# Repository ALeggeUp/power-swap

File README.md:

# PowerSwap

Project work from The Online Electronics Aprenticeship program at [Contextual Electronics](https://contextualelectronics.com/)

# License

This work is licensed under the Creative Commons Attribution 4.0 International License. To view a copy of this license, visit http://creativecommons.org/licenses/by/4.0/ or send a letter to Creative Commons, PO Box 1866, Mountain View, CA 94042, USA.

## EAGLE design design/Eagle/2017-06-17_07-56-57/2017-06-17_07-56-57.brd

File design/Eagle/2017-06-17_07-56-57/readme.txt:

**********************************************************
*************  Important Instructions Follow  ************
**********************************************************
 
All files exported to: Z:\\29\\16\\291644\\6\Eagle\2017-06-17_07-56-57\2017-06-17_07-56-57.xml

**********************************************************
*****************Schematic Instructions  *******************
**********************************************************

To import your new Schematic file into Eagle:

1. Unzip the downloaded folder files to local directory and Start Eagle.
2. Select "File"->"Open"->"Schematic..." from the menu at the top of
the screen.
3. Browse to your newly exported file and select the ".sch" file extension.
4. You should now see your schamtic available in Eagle.

**********************************************************
*******************  PCB Instructions  *******************
**********************************************************

To import your new BOARD file into Eagle:

1. Unzip the downloaded folder files to local directory and Start Eagle.
2. Select "File"->"Open"->"Board..." from the menu at the top of
the screen.
3. Browse to your newly exported file and select the ".brd" file extension.
4. Planes will need to be repoured to update the polygon fills
	1. Once your board is loaded, type "ratsnest" into the command
	   line and press the Enter key.
	2. The polygons should all be filled now.
5. You should now have an image of your board available in Eagle.

**********************************************************
*******************  LIB Instructions  *******************
**********************************************************

To import your new library into Eagle:

1. Start Eagle.
2. Select "File"->"New"->"Library" from the menu.
3. In the blank library window, select "File" -> "Execute Script"
from the menu.
5. Browse to your newly exported Eagle Script file (".scr" file extension)
6. After opening the file, the script will populate the new library.
Layer 93 should NOT exist.
7. Use "File"->Save As: "AcceleratedDesigns_Lib.lbr" and to the desired
location in Eagle native format.
8. Update schematic with the imported library, Select Library and click on Update; open the library file
	and sync. each part.

For additional information, please visit this site:
http://www.accelerated-designs.com/help/Eagle_import.html

You may also find this video helpful:
http://youtu.be/5jGuWY-Yy3Q

**********************************************************
**********************************************************
**********************************************************

Padstack "R1062000220000000P00200P00000" renamed to "R106200022000000"
Component "CRCW040210K2FKED" renamed to "CRCW040210K2FKED"
Component "GRM32ER61E226KE15L" renamed to "GRM32ER61E226KE15L"
Component "08053C104KAT2A" renamed to "08053C104KAT2A"
Component "C3216JB1A476M" renamed to "C3216JB1A476M"
Component "VLP8040T-3R3N" renamed to "VLP8040T-3R3N"
Component "CRCW040256K2FKED" renamed to "CRCW040256K2FKED"
Component "TP-1502" renamed to "TP-1502"
Component "TPS563200DDCR" renamed to "TPS563200DDCR"
The Symbol TPS563200DDC was missing a RefDes attribute, a refdes was created for the symbol.
The Symbol TPS563200DDC was missing a Type attribute, a type was created for the symbol.
The Symbol TPS563200DDC was missing a Value attribute, a value was created for the symbol.

Ultra Librarian Gold 8.1.204 Process Report

Message - Padstack "RX22Y24D0T" Shape(4) is a CIRCLE with no diameter.
Message - Padstack "RX44Y106D0T" Shape(4) is a CIRCLE with no diameter.
Message - Padstack "RX44Y57D0T" Shape(4) is a CIRCLE with no diameter.
Message - Padstack "RX44Y71D0T" Shape(4) is a CIRCLE with no diameter.
Message - Padstack "RX130Y323D0T" Shape(4) is a CIRCLE with no diameter.
Message - Padstack "R106200022000000" Shape(4) is a CIRCLE with no diameter.
Message - Component "CRCW040210K2FKED" attribute "Resistance" references text style "" that is not in the database.
The default pattern text style "H50s3" was substituted.
Message - Component "CRCW040210K2FKED" attribute "Power" references text style "" that is not in the database.
The default pattern text style "H50s3" was substituted.
Message - Component "CRCW040210K2FKED" attribute "Tolerance" references text style "" that is not in the database.
The default pattern text style "H50s3" was substituted.
Message - Component "GRM32ER61E226KE15L" attribute "Cap" references text style "" that is not in the database.
The default pattern text style "H50s3" was substituted.
Message - Component "GRM32ER61E226KE15L" attribute "ESR" references text style "" that is not in the database.
The default pattern text style "H50s3" was substituted.
Message - Component "GRM32ER61E226KE15L" attribute "IRMS" references text style "" that is not in the database.
The default pattern text style "H50s3" was substituted.
Message - Component "GRM32ER61E226KE15L" attribute "VDC" references text style "" that is not in the database.
The default pattern text style "H50s3" was substituted.
Message - Component "08053C104KAT2A" attribute "Cap" references text style "" that is not in the database.
The default pattern text style "H50s3" was substituted.
Message - Component "08053C104KAT2A" attribute "ESR" references text style "" that is not in the database.
The default pattern text style "H50s3" was substituted.
Message - Component "08053C104KAT2A" attribute "IRMS" references text style "" that is not in the database.
The default pattern text style "H50s3" was substituted.
Message - Component "08053C104KAT2A" attribute "VDC" references text style "" that is not in the database.
The default pattern text style "H50s3" was substituted.
Message - Component "C3216JB1A476M" attribute "Datasheet URL" references text style "" that is not in the database.
The default pattern text style "H50s3" was substituted.
Message - Component "C3216JB1A476M" attribute "Cap" references text style "" that is not in the database.
The default pattern text style "H50s3" was substituted.
Message - Component "C3216JB1A476M" attribute "ESR" references text style "" that is not in the database.
The default pattern text style "H50s3" was substituted.
Message - Component "C3216JB1A476M" attribute "IRMS" references text style "" that is not in the database.
The default pattern text style "H50s3" was substituted.
Message - Component "C3216JB1A476M" attribute "VDC" references text style "" that is not in the database.
The default pattern text style "H50s3" was substituted.
Message - Component "VLP8040T-3R3N" attribute "Datasheet URL" references text style "" that is not in the database.
The default pattern text style "H50s3" was substituted.
Message - Component "VLP8040T-3R3N" attribute "L" references text style "" that is not in the database.
The default pattern text style "H50s3" was substituted.
Message - Component "VLP8040T-3R3N" attribute "DCR" references text style "" that is not in the database.
The default pattern text style "H50s3" was substituted.
Message - Component "VLP8040T-3R3N" attribute "IDC" references text style "" that is not in the database.
The default pattern text style "H50s3" was substituted.
Message - Component "CRCW040256K2FKED" attribute "Resistance" references text style "" that is not in the database.
The default pattern text style "H50s3" was substituted.
Message - Component "CRCW040256K2FKED" attribute "Power" references text style "" that is not in the database.
The default pattern text style "H50s3" was substituted.
Message - Component "CRCW040256K2FKED" attribute "Tolerance" references text style "" that is not in the database.
The default pattern text style "H50s3" was substituted.

TextStyle count:  24
Padstack count:   9
Pattern count:    7
Symbol count:     5
Component count:  8

Export

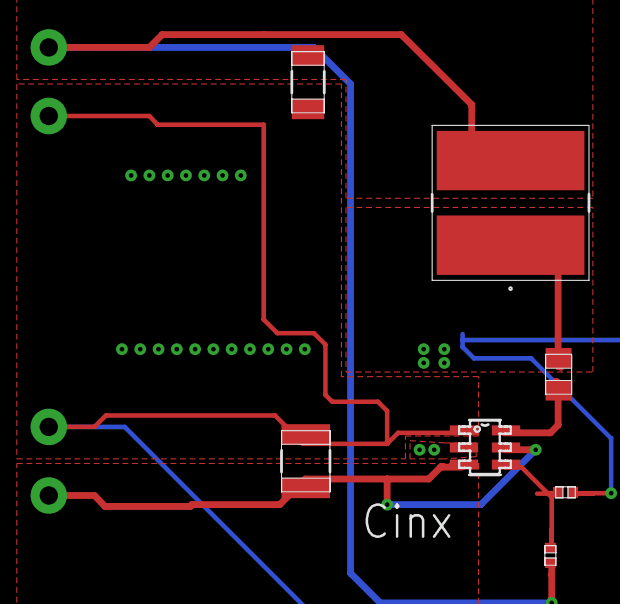
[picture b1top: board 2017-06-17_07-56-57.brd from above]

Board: 4 copper layers, 11 parts (0 on the bottom side), 6 nets.

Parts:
Cbst: 0805
Cin: 1210
Cout: 1206
GND, GND1: TP-1502
L1: VLP8040
Rfbb: 0402
Rfbt: 0402
U1: DDC0006A
VIN: TP-1502
VOUT: TP-1502

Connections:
0: Cin.2, Cout.2, GND.1, GND1.1, Rfbb.2, U1.1
3: Rfbb.1, Rfbt.2, U1.4
5: Cbst.1, L1.1, U1.2
6: Cout.1, L1.2, Rfbt.1, VOUT.1
8: Cin.1, U1.3, U1.5, VIN.1
9: Cbst.2, U1.6

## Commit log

2017-06-17 Initial commit with EAGLE exports from WEBENCH
